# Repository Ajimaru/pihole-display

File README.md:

# pihole-display

OLED display controller for a **BeagleBone Black** running **Pi-hole** and **Unbound**.  
Shows DNS filter statistics, system info and allows basic control via 4 hardware buttons —
or from a browser, through a built-in web UI that mirrors the display.

## Features

- Five screens: Pi-hole stats, Unbound cache, network, system health, service status
- Control from four hardware buttons: pause or disable blocking, update gravity,
  flush caches, restart services, reboot or shut down
- Built-in web UI that mirrors the display and makes the buttons clickable,
  behind a login
- Flags available Pi-hole updates and can install them
- Screen lock and sleep timeout, both configurable

## Hardware

- Component: SBC
  Details: BeagleBone Black (Debian 13 Trixie)
- Component: Display
  Details: 0.96" OLED SSD1315, 128x64, I2C
- Component: Buttons
  Details: 4x directly wired (K1-K4), 4.7K pull-up on board
- Component: Interface
  Details: I2C2 (P9_19 SCL, P9_20 SDA) + 4x GPIO (P8_7-P8_10)

### Wiring

```text
Display Pin  →  BBB Pin     Function
───────────────────────────────────────
GND          →  P9 Pin 2    Ground
VCC          →  P9 Pin 4    3.3V
SCL          →  P9 Pin 19   I2C2 SCL
SDA          →  P9 Pin 20   I2C2 SDA
K1  (v)      →  P8 Pin 7    gpiochip1 line 2
K2  (^)      →  P8 Pin 8    gpiochip1 line 3
K3  (#)      →  P8 Pin 9    gpiochip1 line 5
K4  (*)      →  P8 Pin 10   gpiochip1 line 4
```

The display is mounted rotated by 180° (`DISPLAY_ROTATE = 2`), so K2 is
up and K1 is down.

**-> Detailed wiring guide with perfboard adapter: [docs/WIRING_GUIDE.md](docs/WIRING_GUIDE.md)**

## Enclosure

[`stl/BBB_Cover.stl`](stl/BBB_Cover.stl) is a printable cover that frames the
OLED display (58 × 35 × 6.5 mm). It is designed to go with the
[BeagleBone Black Case with Ventilation](https://www.thingiverse.com/thing:1644922)
by MandyRae on Thingiverse.

## Installation

### Prerequisites: Pi-hole and Unbound

pihole-display expects Pi-hole v6 with Unbound as its local upstream resolver
on the BBB. Set both up first with the official Pi-hole documentation:

- [Pi-hole prerequisites](https://docs.pi-hole.net/main/prerequisites/)
- [Pi-hole installation](https://docs.pi-hole.net/main/basic-install/)
- [Unbound as a recursive DNS server for Pi-hole](https://docs.pi-hole.net/guides/dns/unbound/)

### Install pihole-display

From a release (recommended) — the archive holds everything needed on the
board, including the wiring guide:

```bash
# On the BBB — picks up whatever the latest release is
REPO=Ajimaru/pihole-display
VERSION=$(curl -fsSL "https://api.github.com/repos/${REPO}/releases/latest" |
          sed -n 's/.*"tag_name": *"v\([^"]*\)".*/\1/p')
echo "Installing v${VERSION}"

BASE="https://github.com/${REPO}/releases/download/v${VERSION}"
curl -fsSLO "${BASE}/pihole-display-${VERSION}.tar.gz"
curl -fsSLO "${BASE}/pihole-display-${VERSION}.tar.gz.sha256"
# Compare the hash itself, so this works regardless of the path the
# checksum file records.
[ "$(awk '{print $1}' "pihole-display-${VERSION}.tar.gz.sha256")" \
  = "$(sha256sum "pihole-display-${VERSION}.tar.gz" | awk '{print $1}')" ] \
  && echo "checksum OK" || echo "CHECKSUM MISMATCH"

tar -xzf "pihole-display-${VERSION}.tar.gz"
cd "pihole-display-${VERSION}"
sudo ./install.sh
```

To install a specific version instead, set `VERSION=0.1.0` by hand and skip
the `curl` that looks it up.

Or straight from a checkout, to run unreleased changes:

```bash
# Copy to BeagleBone Black (root login is disabled on the BeagleBoard images)
scp -r pihole-display/ <user>@<BBB_IP_ADDRESS>:/tmp/

# On the BBB
cd /tmp/pihole-display
sudo ./install.sh

# Verify I2C (should show 3c, or 3d if the address bridge is set)
sudo i2cdetect -y -r 2

# Start
sudo systemctl start pihole-display
sudo journalctl -u pihole-display -f
```

#### Updating an existing installation

Fetch and unpack the new release exactly like a fresh install — the same
commands above, including the checksum check — then run `install.sh` from the
new directory. It upgrades `/opt` in place.

The running service keeps the old code until it is restarted, so finish with:

```bash
sudo systemctl restart pihole-display
journalctl -u pihole-display -n 20 --no-pager
```

Site settings are not affected: they live in `/etc/pihole-display/config.py`,
which the installer never overwrites. Settings a new release adds simply keep
their default until you assign them, so there is no merge step and the service
cannot fail on a missing attribute.

When updating from a version that still kept settings in
`/opt/pihole-display/config.py`, the installer carries that file over to
`/etc/pihole-display/config.py` (mode `0600`) once. If both exist, the `/etc`
file wins; the old copy is saved to `/var/backups/pihole-display/` and the
`diff` command is printed, so you can see what you had.

Runtime state (`state.json`, the web password file) lives in
`/var/lib/pihole-display` and is never touched by the installer.

The web UI is then available at `http://<BBB_IP_ADDRESS>:8080` — log in with
`admin` / `pihole` and change the password straight away (see [Web UI](#web-ui)).

The Unbound screen reads its stats with `unbound-control`, which Debian ships
disabled. `install.sh` offers to enable it (this restarts Unbound, so DNS is
briefly unavailable for the network). To do it manually, through a local
socket without certificates:

```bash
sudo cp /etc/unbound/unbound.conf.d/remote-control.conf.dpkg-dist \
        /etc/unbound/unbound.conf.d/remote-control.conf
sudo unbound-checkconf && sudo systemctl restart unbound
```

## Usage

Once the service runs, the display cycles through five screens. Each one has
an action menu behind the `#` key, and anything reachable there is also
reachable from the [web UI](#web-ui).

### Screens

- Pi-hole
  Description: Block %, queries, clients
  Action key (#): Pause / disable / gravity / flush cache menu
- Unbound
  Description: Cache hit %, Q/s, total
  Action key (#): Cache / restart menu
- Network
  Description: IP, gateway, hostname, uptime
  Action key (#): -
- System
  Description: CPU %, temp, RAM, disk (temp shows `--` without a sensor,
  the BBB kernel has none)
  Action key (#): Reboot / shutdown / screen lock menu
- Status
  Description: Service health overview, plus `update` next to Pi-hole when
  a newer Core, Web or FTL release is out
  Action key (#): Actions menu, including `Update Pi-hole` when one is
  available

#### Button layout

```text
K2 (^)  short  → previous screen / menu up
K1 (v)  short  → next screen     / menu down
K3 (#)  short  → open action menu / confirm
K4 (*)  short  → home screen     / cancel
K2 (^)  long   → force data refresh
K1 (v)  long   → toggle display sleep
K4 (*)  long   → home screen
K4 (*)  hold 5s → wake the display while the screen lock is on
```

The display sleeps after `DISPLAY_TIMEOUT` without input. Any button
wakes it, unless the screen lock is on: then only holding * for 5 seconds
does. Long running actions such as a Pi-hole update hold it on until they
finish, so the screen never blanks mid-update. The System menu (#) offers reboot, shutdown and the screen lock
toggle, each with a yes/no confirmation. The lock setting is kept in
`/var/lib/pihole-display/state.json`.

### Pi-hole updates

The Status screen shows `update` next to Pi-hole when Core, Web or FTL has a
newer release, the same information the admin page puts in its footer. It is
read from `GET /api/info/version` once an hour (`UPDATE_CHECK_INTERVAL`),
since versions rarely change.

When an update is available, the Status action menu (`#`) gains an
`Update Pi-hole` entry that runs `pihole -up` after a yes/no prompt.

## Web UI

The service runs a small web server that mirrors the OLED and turns the four
hardware buttons into clickable ones. It is reachable on port 8080 per default:

```text
http://<BBB_IP_ADDRESS>:8080
```

The page shows the live display, scaled up, with the four keys down its right
side. They are ordered by what they do — up above down — and each keeps its
board marking, so the top key reads `K2` because the display is mounted
upside down.

Pressing and holding works like it does on the board: the server measures how
long a key is held and classifies it with the same thresholds as the GPIO
handler, so short press, long press and the 5-second hold to wake a locked
screen all behave identically. Below 560 px the keys move under the display
into a row.

### First login

```text
Username: admin
Password: pihole
```

**The password must be changed on first login** — no other page is reachable
until it is. Until then, the service logs a warning on every start and the web
page shows a warning banner.

The user name is matched without regard to case, and leading or trailing
spaces are stripped from both fields, so a pasted password does not fail over
an invisible space. While the default password is still set, the login form
asks the browser not to autofill it — a saved password from an earlier install
otherwise looks like a wrong one.

### Security

- **The connection is plain HTTP.** The password is sent across the network in
  the clear. This is meant for a trusted home LAN. Over anything else, use an
  SSH tunnel and bind to localhost (see below).
- The default password `admin` / `pihole` is public — it is in this README.
  Change it immediately, and do not expose port 8080 to the internet.
- Passwords are stored as PBKDF2-SHA256 hashes (200,000 iterations, random
  salt) in `/var/lib/pihole-display/web_auth.json`, mode `0600`.
- Sessions are kept in memory only, so restarting the service logs everyone out.
- After 5 failed logins an IP is locked out for 60 seconds.

To restrict access to an SSH tunnel, set `WEB_HOST = '127.0.0.1'` in
`/etc/pihole-display/config.py` and connect with:

```bash
ssh -L 8080:localhost:8080 <user>@<BBB_IP_ADDRESS>
```

To turn the web UI off entirely, set `WEB_ENABLED = False`.

The systemd unit is hardened (`ProtectHome`, `PrivateTmp`,
`ProtectKernelTunables`, `RestrictAddressFamilies`), but deliberately does
**not** set `NoNewPrivileges` or `RestrictSUIDSGID`: `pihole -up` drops to
the `pihole` user and uses setuid `sudo` to get back to root. With either
flag on, the update aborts after stopping FTL and leaves the network without
DNS.

## Configuration

Site settings live in `/etc/pihole-display/config.py` (mode `0600`, root
only), which is loaded on top of the shipped defaults in
`/opt/pihole-display/config.py`. Assign only the names you want to change —
everything else keeps its default, so a new release can add settings without
breaking your file. After editing, restart the service:

```bash
sudo systemctl restart pihole-display
```

The installer creates the file when it finds settings in an old
`/opt/pihole-display/config.py`, and never overwrites it afterwards.

Example (all of it optional, defaults shown):

```python
I2C_PORT         = 2           # /dev/i2c-2
I2C_ADDRESS      = 0x3C        # or 0x3D
DISPLAY_ROTATE   = 2           # 180°, display mounted upside down
PIHOLE_HOST      = 'localhost' # Pi-hole host
PIHOLE_SCHEME    = 'http'      # 'https' when Pi-hole redirects HTTP to HTTPS
PIHOLE_TLS_VERIFY = True       # CA file path, or False for self-signed
PIHOLE_PASSWORD  = ''          # Pi-hole v6; empty = log in with /etc/pihole/cli_pw
REFRESH_INTERVAL = 10          # seconds
UPDATE_CHECK_INTERVAL = 3600   # seconds between Pi-hole update checks
DISPLAY_TIMEOUT  = 60          # seconds until sleep (0 = never)
HOLD_MS          = 5000        # hold * this long to wake a locked display

WEB_ENABLED      = True        # False disables the web UI entirely
WEB_HOST         = '0.0.0.0'   # '127.0.0.1' = local only (SSH tunnel)
WEB_PORT         = 8080        # Pi-hole admin already uses :80
WEB_USER         = 'admin'     # Login name
WEB_SCALE        = 4           # Display zoom in the browser
```

Since Pi-hole v6 redirects HTTP to HTTPS by default, point the app straight at
TLS. With the self-signed certificate, either trust Pi-hole's CA file or turn
verification off for the local connection:

```python
PIHOLE_HOST       = 'pi.hole'              # matches the certificate's SAN
PIHOLE_SCHEME     = 'https'
PIHOLE_TLS_VERIFY = '/etc/pihole/tls_ca.crt'
```

With `PIHOLE_PASSWORD` empty, the service logs in with Pi-hole's local CLI
password file, so no password has to be stored in the settings file.

### HTTPS

The web UI speaks plain HTTP by default. To serve it over TLS, point
`WEB_TLS_CERT` at a PEM file — a combined certificate and private key works,
a separate key can be supplied through `WEB_TLS_KEY`:

```python
WEB_PORT               = 8443
WEB_TLS_CERT           = '/etc/pihole/tls.pem'  # Pi-hole's self-signed cert
WEB_HTTP_REDIRECT_PORT = 8080                  # plain HTTP -> HTTPS
```

The redirect listener answers every plain request with `301 Moved
Permanently` to the TLS port, keeping the path. As soon as a certificate is
configured, the session cookie carries the `Secure` flag. Leave
`WEB_TLS_CERT` empty to go back to plain HTTP; `WEB_HTTP_REDIRECT_PORT = 0`
disables the redirect listener.

The certificate is not validated against a CA — browsers warn on the
self-signed Pi-hole certificate. Accessing the UI as `https://pi.hole:8443`
matches its `CN` and avoids that warning on machines using Pi-hole for DNS.

## Development

### Project structure

```text
pihole-display/
├── config.py              — pins, I2C bus, timing
├── data.py                — Pi-hole API v5/v6, Unbound, system stats
├── display_manager.py     — OLED screens + menu system (luma.oled)
├── button_handler.py      — GPIO buttons (gpiod v2 + sysfs fallback)
├── web_server.py          — web UI: display mirror + clickable buttons
├── web_auth.py            — login, PBKDF2 passwords, sessions
├── web_ui.py              — HTML/CSS/JS for the web UI (served inline)
├── main.py                — main loop + event handling
├── version.py             — version number (shown in the System header)
├── requirements.txt       — Python dependencies
├── pihole-display.service — systemd unit
└── install.sh             — installation script

docs/
├── WIRING_GUIDE.md        — wiring, verification, troubleshooting
├── generate_mockups.py    — renders all screens as PNG (run on the BBB)
├── mockups/               — rendered screen mockups
└── kicad/                 — KiCad PCB for the cape

scripts/
├── release.sh             — set version.py, commit and tag a release
└── changelog.py           — group commits into release notes

stl/
└── BBB_Cover.stl          — printable cover around the OLED display
```

### Releases

A release is cut by pushing a tag. `scripts/release.sh` sets `version.py`,
commits and tags in one step, so the tag and the version the display shows
can never drift apart:

```bash
./scripts/release.sh 0.2.0 --dry-run   # show what it would do
./scripts/release.sh 0.2.0             # set version, commit, tag
git push origin main v0.2.0            # this publishes the release
```

Pushing the tag starts [`.github/workflows/release.yml`](.github/workflows/release.yml),
which refuses to build if the tag and `version.py` disagree, then packs
`pihole-display-<version>.tar.gz` with the modules, `install.sh`, the
systemd unit, the licenses and the wiring guide, adds a `.sha256` next to
it, and publishes a GitHub release. The notes are grouped from the commit
subjects by their Conventional Commits prefix (`feat:`, `fix:`, `docs:`,
…); anything without a prefix is listed under "Other", and a `!` marks a
breaking change.

To preview the notes before tagging:

```bash
git log --no-merges --pretty=$'%s\t%h' v0.1.0..HEAD |
  VERSION=0.2.0 python3 scripts/changelog.py
```

### Screen gallery

Rendered by [`docs/generate_mockups.py`](docs/generate_mockups.py), which
drives the real `DisplayManager` against a dummy device. Run it on the board
(it needs luma and the DejaVu fonts) after changing anything a screen shows.

> All screens rendered at 4× scale (actual display: 128×64 px)

<details>
<summary>Show all screen mockups</summary>

#### Main screens

- Splash:

- Pi-hole active:

- Pi-hole paused:

- Pi-hole off:

- Unbound:

- Unbound (error):

- Network:

- System:

- Status:

- Status (error):

- Status (update available):

#### Menus

- Pi-hole menu:

- Pi-hole menu (scrolled):

- Pi-hole menu (off):

- Unbound menu:

- Status actions:

- Status actions (scrolled):

- Status actions (update available):

- System menu:

- Confirmation (reboot):

#### Status messages

- Pause:

- Active:

- Off:

- Flush:

- Gravity update:

- Reboot:

- Screen lock on:

- Updating:

- Update done:

</details>

## Dependencies

- [luma.oled](https://github.com/rm-hull/luma.oled)
  Version: >= 3.13
  License: MIT
  Purpose: OLED driver (SSD1306/SSD1315)
- [Pillow](https://python-pillow.org/)
  Version: >= 12.1.1
  License: MIT-CMU
  Purpose: Image/text rendering
- [psutil](https://github.com/giampaolo/psutil)
  Version: >= 5.9
  License: BSD-3
  Purpose: System stats (CPU, RAM, disk)
- [requests](https://docs.python-requests.org/)
  Version: >= 2.33.0
  License: Apache-2.0
  Purpose: Pi-hole API calls
- [python-gpiod](https://git.kernel.org/pub/scm/libs/libgpiod/libgpiod.git/)
  Version: system
  License: LGPL-2.1
  Purpose: GPIO button reading

The web UI adds no dependency: it is built entirely on the Python standard
library (`http.server`, `hashlib`, `secrets`) and reuses Pillow, which is
already needed for rendering.

System packages (installed by `install.sh`): `python3-venv`,
`python3-libgpiod`, `gpiod`, `i2c-tools`, `libi2c-dev`, `fonts-dejavu-core`

Full attribution for each of these is in
[THIRD_PARTY_LICENSES.md](THIRD_PARTY_LICENSES.md).

## License

MIT — see [LICENSE](LICENSE).

The libraries this project builds on carry their own licenses, listed in
[THIRD_PARTY_LICENSES.md](THIRD_PARTY_LICENSES.md).

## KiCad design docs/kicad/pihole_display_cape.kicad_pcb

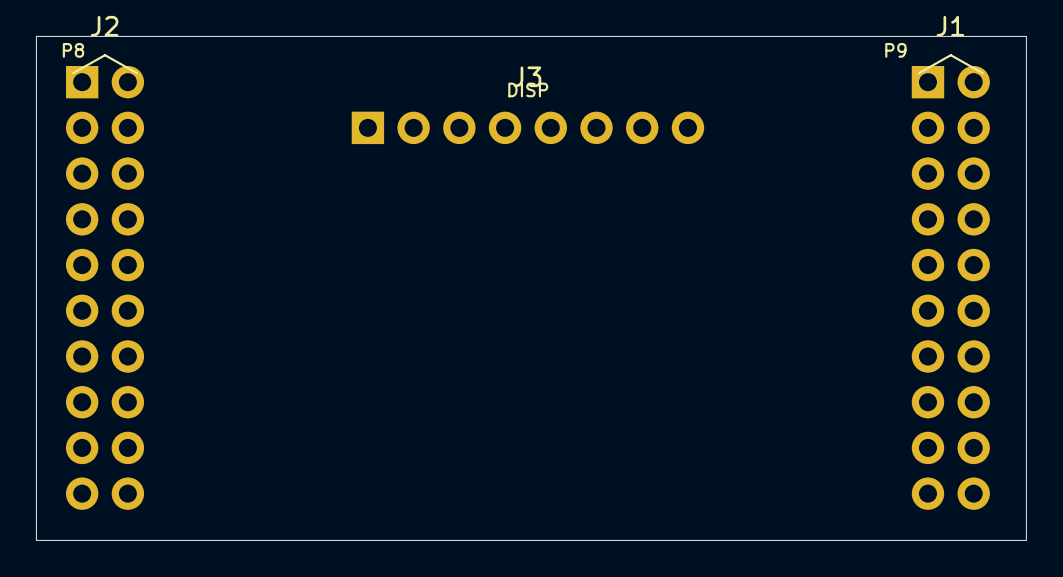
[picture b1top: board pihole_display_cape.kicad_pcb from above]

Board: 2 copper layers, 55.0 x 28.0 mm, 3 parts (0 on the bottom side), 8 nets, no tracks yet.

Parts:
J1: P9_1-20; J1
J2: P8_1-20; J2
J3: DISP_1x8; J3

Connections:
/+3.3V: J1.3, J1.4, J3.2
/BTN_K1: J2.7, J3.8
/BTN_K2: J2.8, J3.7
/BTN_K3: J2.9, J3.6
/BTN_K4: J2.10, J3.5
/GND: J1.1, J1.2, J3.1
/SCL: J1.19, J3.3
/SDA: J1.20, J3.4

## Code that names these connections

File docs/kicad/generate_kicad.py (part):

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
# Net assignments for P8 pins (unconnected pins omitted)
_P8_NET: dict[int, str] = {
    7:  '/BTN_K1',   # GPIO2_2  K1 = ^ (up)
    8:  '/BTN_K2',   # GPIO2_3  K2 = v (down)
    9:  '/BTN_K3',   # GPIO2_5  K3 = # (ok)
    10: '/BTN_K4',   # GPIO2_4  K4 = * (back)
}

# Footprint centre for J2
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    '/+3.3V',     # pin 2
    '/SCL',       # pin 3
    '/SDA',       # pin 4
    '/BTN_K4',    # pin 5
    '/BTN_K3',    # pin 6
    '/BTN_K2',    # pin 7
    '/BTN_K1',    # pin 8
]

_DISP_CX = DISP_X1 + 3.5 * PITCH    # 27.305  (centre of 8-pin row)
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
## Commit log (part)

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2026-04-07 chore: enable Dependabot updates
2026-04-07 Refactor and translate code comments and log messages for clarity
    - Updated comments and log messages in button_handler.py, config.py, data.py, display_manager.py, install.sh, and main.py to improve readability and consistency.
    - Translated German comments and messages to English.
    - Standardized terminology across the codebase, such as changing "Aktiv" to "Active" and "Fehler" to "Error".
    - Enhanced clarity in function descriptions and user prompts in the installation script.
2026-04-07 Add new mockup images for menu status and message states
    - Added 14_menu_status_actions.png to represent menu status actions.
    - Added 14b_menu_status_scrolled.png for the scrolled state of the menu.
    - Added 15_message_pause.png to illustrate the message pause state.
    - Added 16_message_active.png for the active message state.
    - Added 17_message_off.png to depict the message off state.
    - Added 18_message_flush.png to show the message flush state.
2026-04-07 Update license year, enhance README button descriptions, and add splash screen to display manager
2026-04-07 Update issue templates
2026-04-07 chore: update file permissions for install.sh and add .gitattributes for shell scripts
2026-04-09 chore: update install.sh file permissions to make it executable
2026-04-09 Add KiCad PCB and project files for Pi-hole display cape
    - Created a new KiCad PCB file `pihole_display_cape.kicad_pcb` with detailed layout including footprints for connectors and pads for buttons.
    - Added a new KiCad project file `pihole_display_cape.kicad_pro` containing design settings, net settings, and other project metadata.
2026-04-10 chore: update install.sh file permissions to restrict access
